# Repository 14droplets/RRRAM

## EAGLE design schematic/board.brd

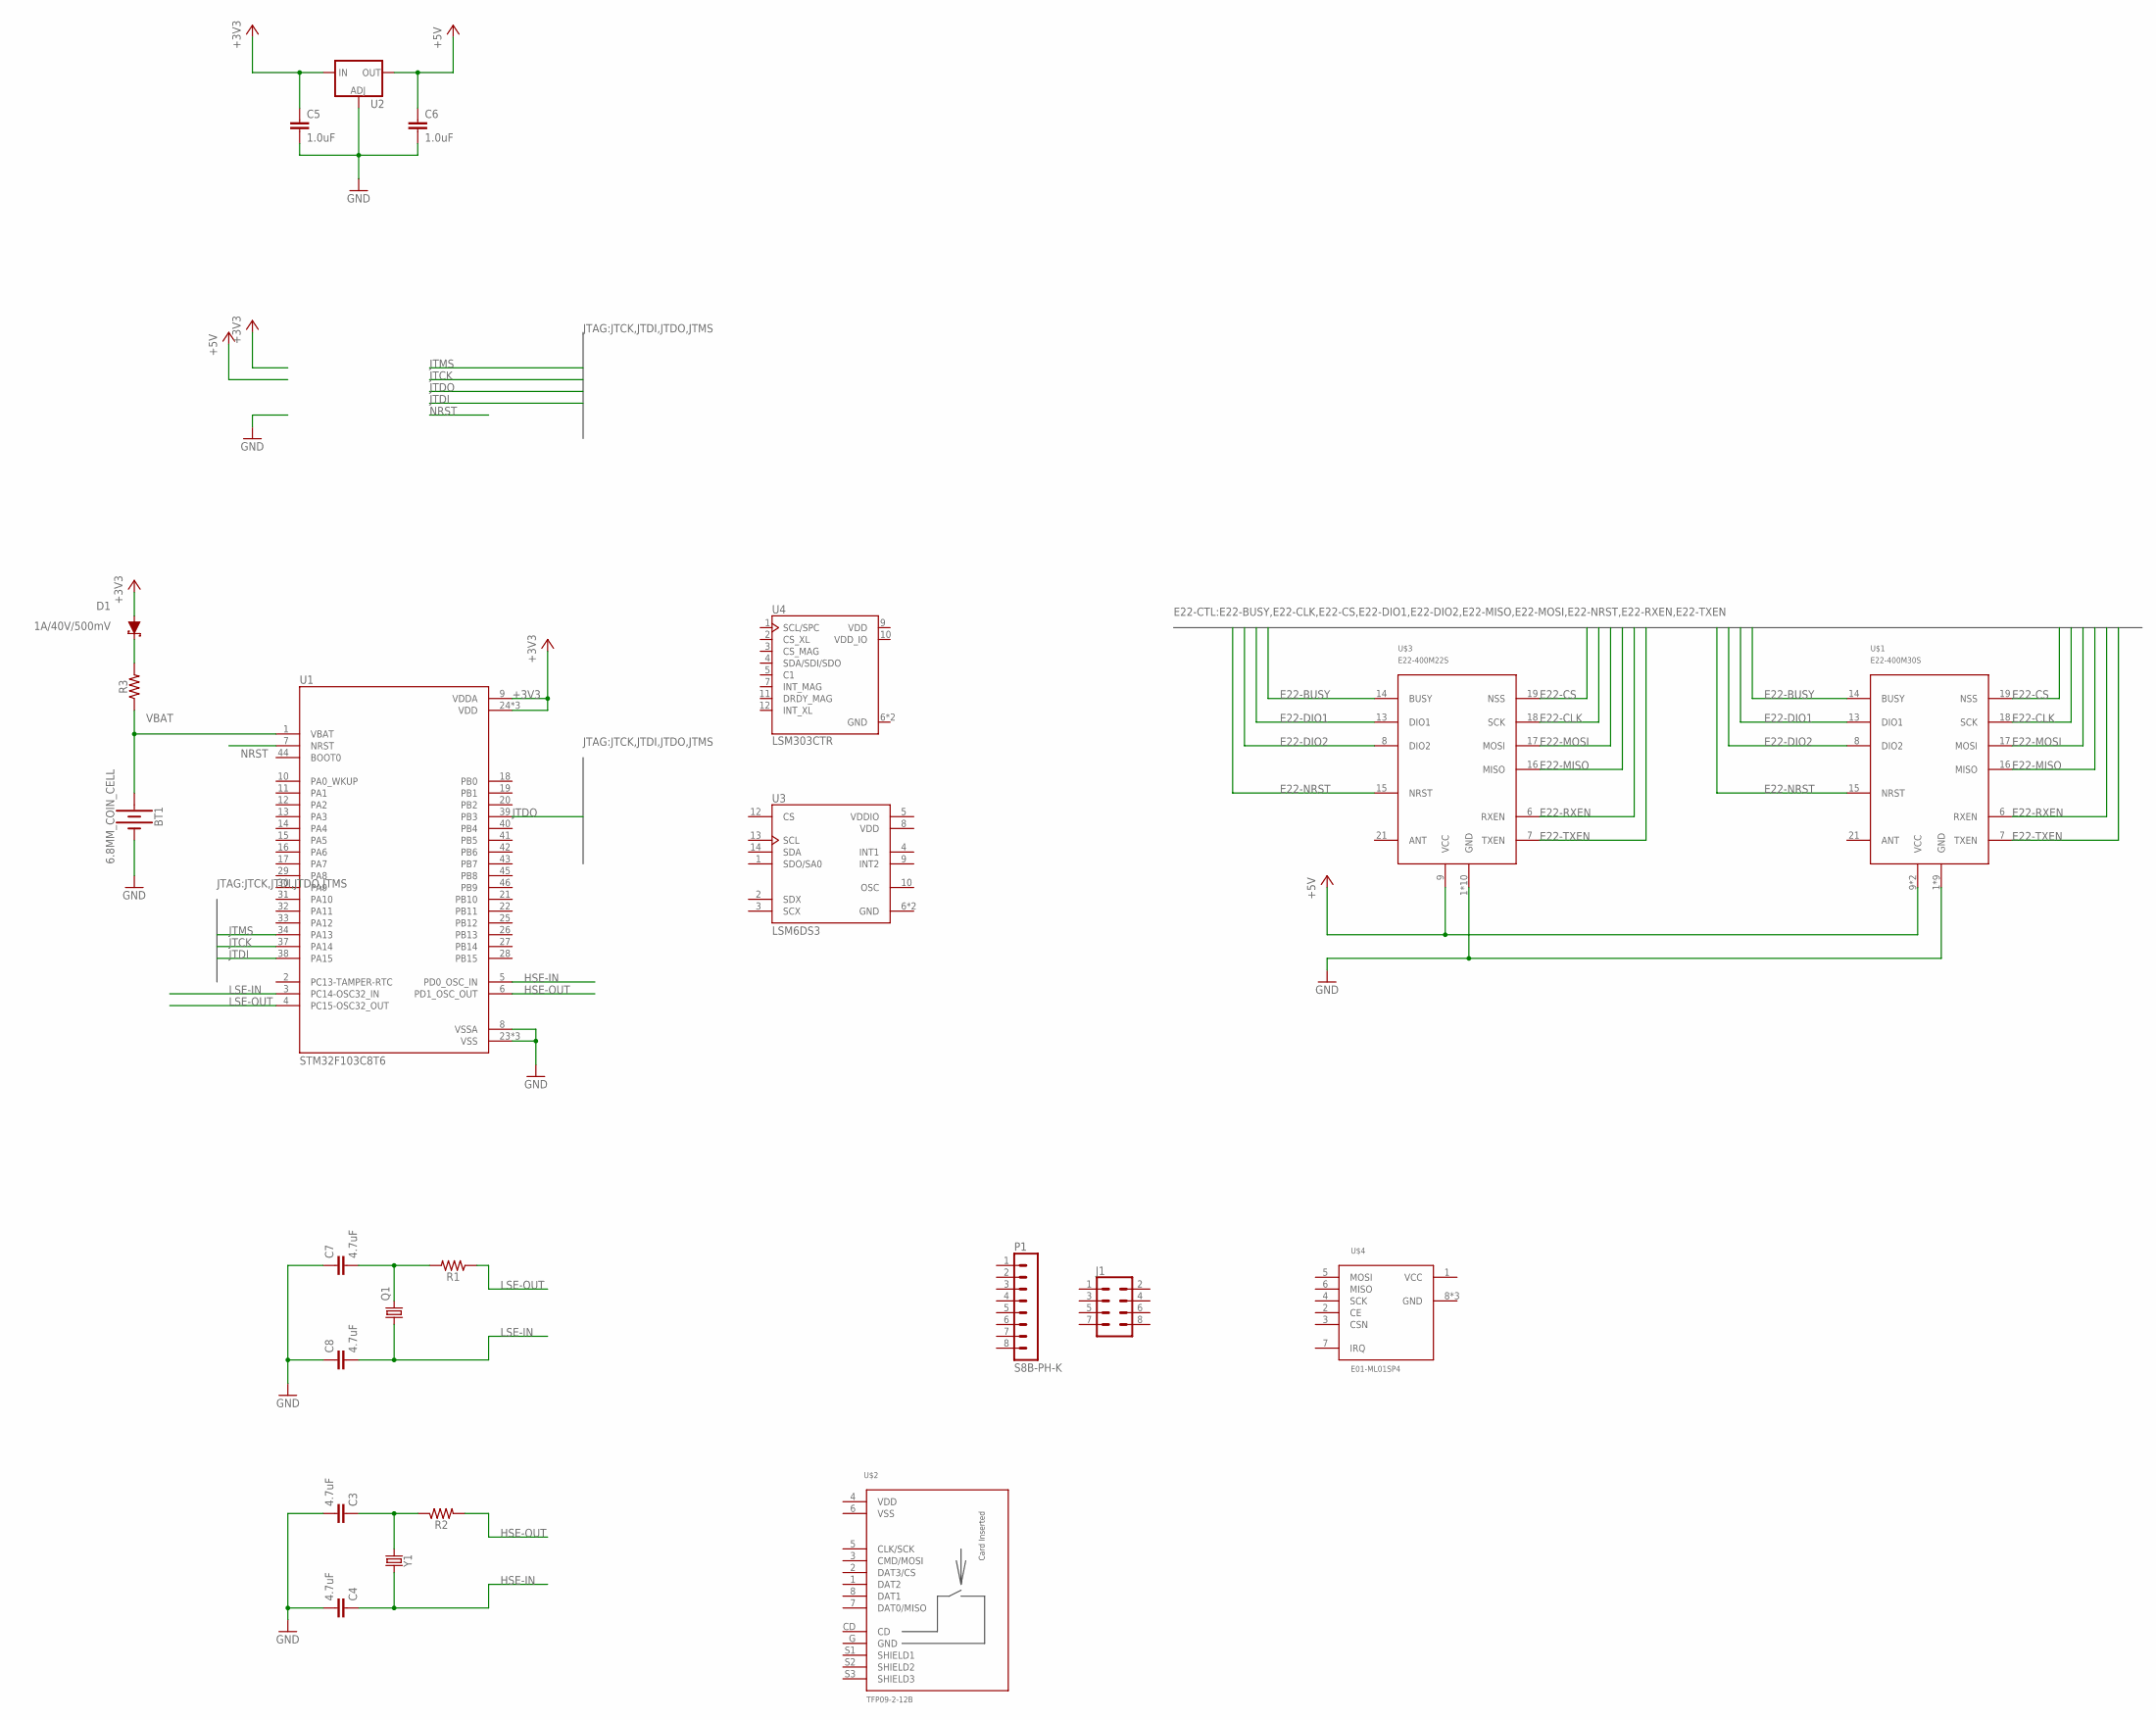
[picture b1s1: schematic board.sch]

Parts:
BT1: 6.8MM_COIN_CELL; BATTCON-6.8MM
C3, C4, C7, C8: 4.7uF; 0603
C5, C6: 1.0uF; 0805
D1: 1A/40V/500mV; SMA-DIODE
J1: CONN_04X2; 2X4
P1: S8B-PH-K
Q1: CRYSTALMM20SS; MM20SS
R1, R2, R3: 0603
U1: STM32F103C8T6; QFP50P900X900X160-48N
U2: V_REG_LM1117SOT223; SOT223
U3: LSM6DS3; PQFN50P300X250X86-14N
U4: LSM303CTR; LGA12R50P_200X200X100
U$1: E22-400M30S
U$2: TFP09-2-12B
U$3: E22-400M22S
U$4: E01-ML01SP4
Y1: CRYSTALPTH-HC49US; HC49US

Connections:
+3V3: C5.1, D1.A, U1.9 (VDDA), U1.24 (VDD), U1.36 (VDD), U1.48 (VDD), U2.3 (IN)
+5V: C6.1, U2.2 (OUT), U2.4 (OUT), U$1.9 (VCC), U$1.10 (VCC), U$3.9 (VCC)
E22-BUSY: U$1.14 (BUSY), U$3.14 (BUSY)
E22-CLK: U$1.18 (SCK), U$3.18 (SCK)
E22-CS: U$1.19 (NSS), U$3.19 (NSS)
E22-DIO1: U$1.13 (DIO1), U$3.13 (DIO1)
E22-DIO2: U$1.8 (DIO2), U$3.8 (DIO2)
E22-MISO: U$1.16 (MISO), U$3.16 (MISO)
E22-MOSI: U$1.17 (MOSI), U$3.17 (MOSI)
E22-NRST: U$1.15 (NRST), U$3.15 (NRST)
E22-RXEN: U$1.6 (RXEN), U$3.6 (RXEN)
E22-TXEN: U$1.7 (TXEN), U$3.7 (TXEN)
GND: BT1.-, C3.2, C4.2, C5.2, C6.2, C7.1, C8.1, U1.8 (VSSA), U1.23 (VSS), U1.35 (VSS), U1.47 (VSS), U2.1 (ADJ), U3.6 (GND), U3.7 (GND), U4.6 (GND), U4.8 (GND), U$1.1 (GND), U$1.2 (GND), U$1.3 (GND), U$1.4 (GND), U$1.5 (GND), U$1.11 (GND), U$1.12 (GND), U$1.20 (GND), U$1.22 (GND), U$3.1 (GND), U$3.2 (GND), U$3.3 (GND), U$3.4 (GND), U$3.5 (GND), U$3.10 (GND), U$3.11 (GND), U$3.12 (GND), U$3.20 (GND), U$3.22 (GND), U$4.8 (GND), U$4.9 (GND), U$4.10 (GND)
HSE-IN: C4.1, U1.5 (PD0_OSC_IN), Y1.1
HSE-OUT: R2.2, U1.6 (PD1_OSC_OUT)
JTCK: U1.37 (PA14)
JTDI: U1.38 (PA15)
JTDO: U1.39 (PB3)
JTMS: U1.34 (PA13)
LSE-IN: C8.2, Q1.1, U1.3 (PC14-OSC32_IN)
LSE-OUT: R1.1, U1.4 (PC15-OSC32_OUT)
unnamed: D1.C, R3.2
unnamed: C7.2, Q1.4 (2), R1.2
unnamed: C3.1, R2.1, Y1.2
NRST: U1.7 (NRST)
VBAT: BT1.+, R3.1, U1.1 (VBAT)
VCC: U$4.1 (VCC)
VDD: U3.8 (VDD), U4.9 (VDD)
VDDIO: U3.5 (VDDIO)
VDD_IO: U4.10 (VDD_IO)

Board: 4 copper layers, 23 parts (12 on the bottom side), 22 nets, no tracks yet.

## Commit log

2019-07-16 муки выбора конденсаторов для VREG
2019-07-16 Кажется, все необходимое для МК нарисовано
2019-07-22 Удалена лишняя либа с регуляторами питания. Добавлен "стандартный" JTAG разъем
2019-07-22 Начерно набросана обвязка мк (без фильтрующих кондеров). Обвязка МК нагло срисована с блюпила без номиналов
2019-07-22 Радиомодули LORA 433
2019-07-22 Модули для NRF24
2019-07-22 Модули для NRF24 в каком-то виде на платах
2019-07-24 Новый вариант разъема для отладки
2019-07-25 Прикидки размеров платы
2019-12-14 Замороженное состояние

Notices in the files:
parts and their libraries:
SparkFun-Capacitors: Licensing: Creative Commons ShareAlike 4.0 International - https://creativecommons.org/licenses/by-sa/4.0
con-jst-ph: Copyright (C) 2016, Bob Starr
